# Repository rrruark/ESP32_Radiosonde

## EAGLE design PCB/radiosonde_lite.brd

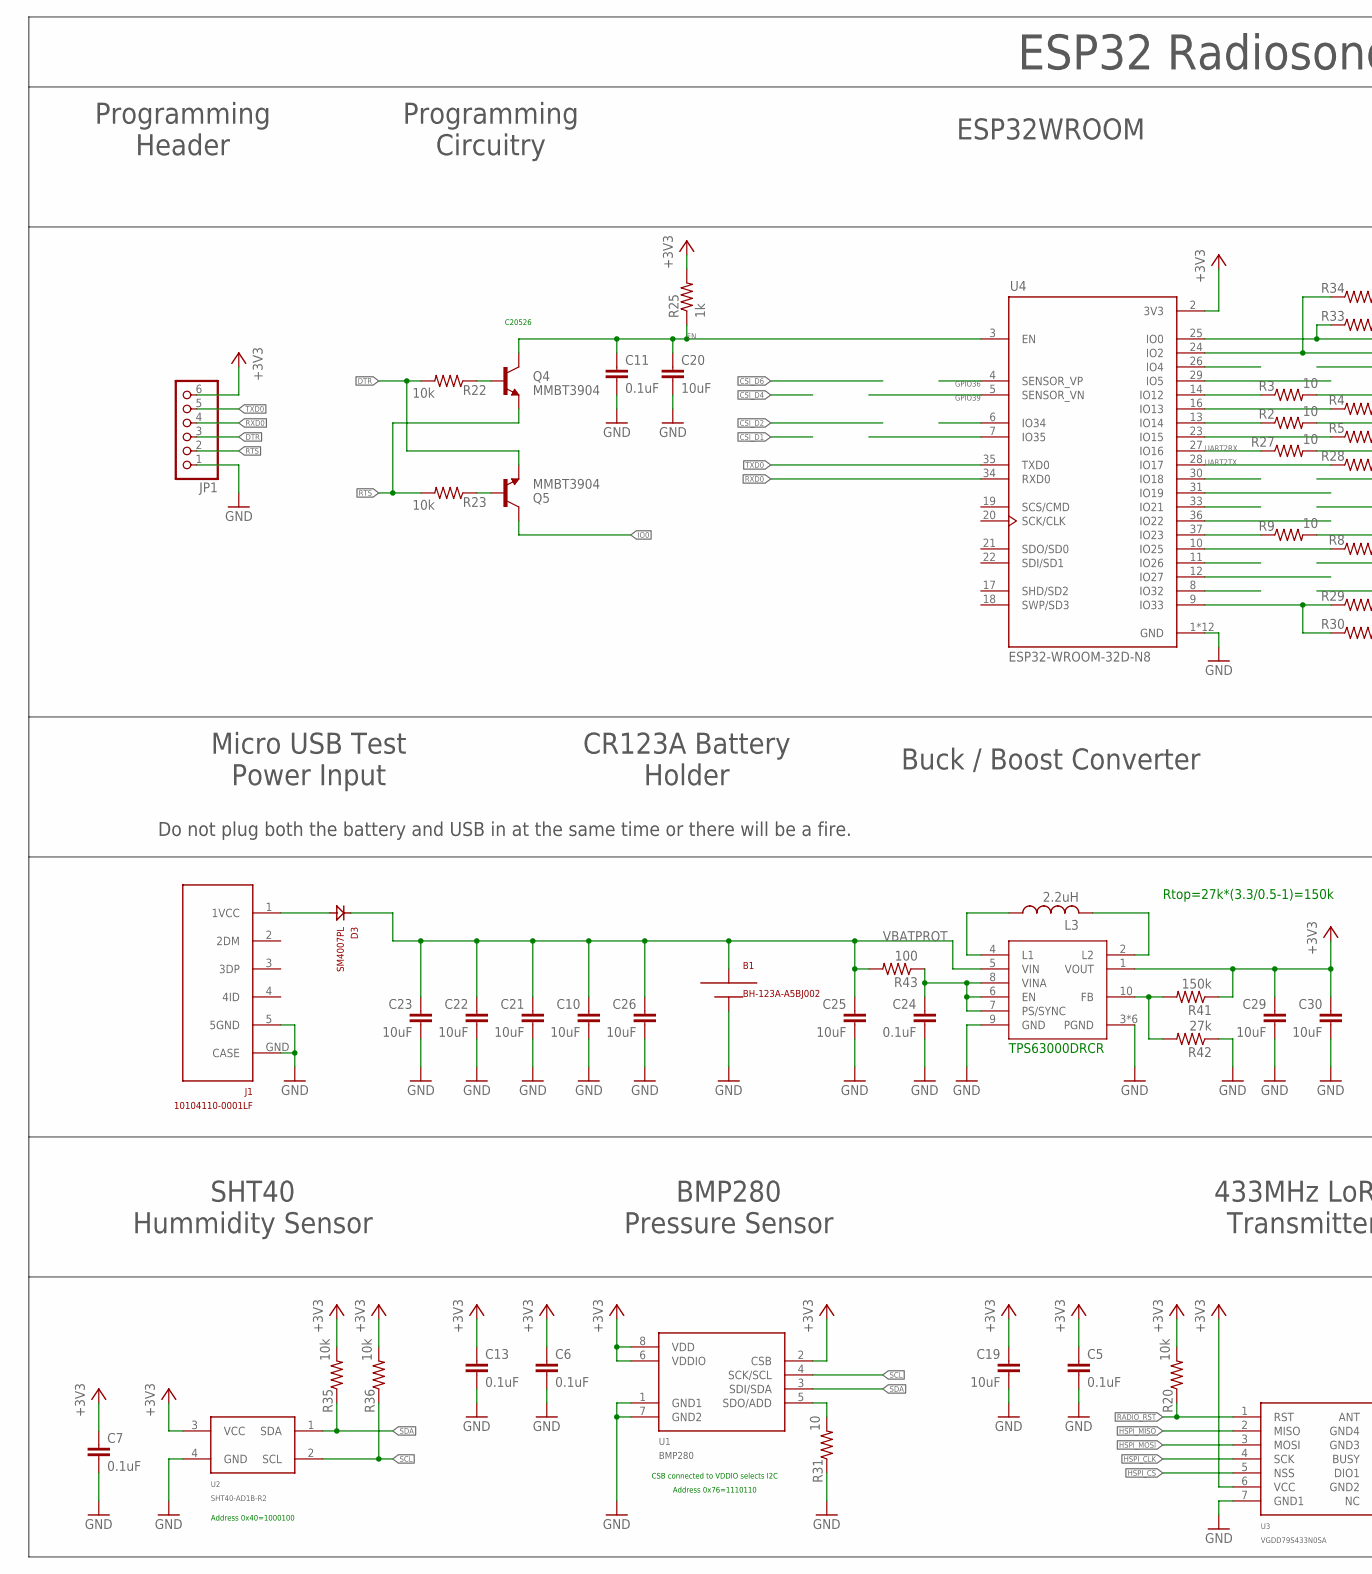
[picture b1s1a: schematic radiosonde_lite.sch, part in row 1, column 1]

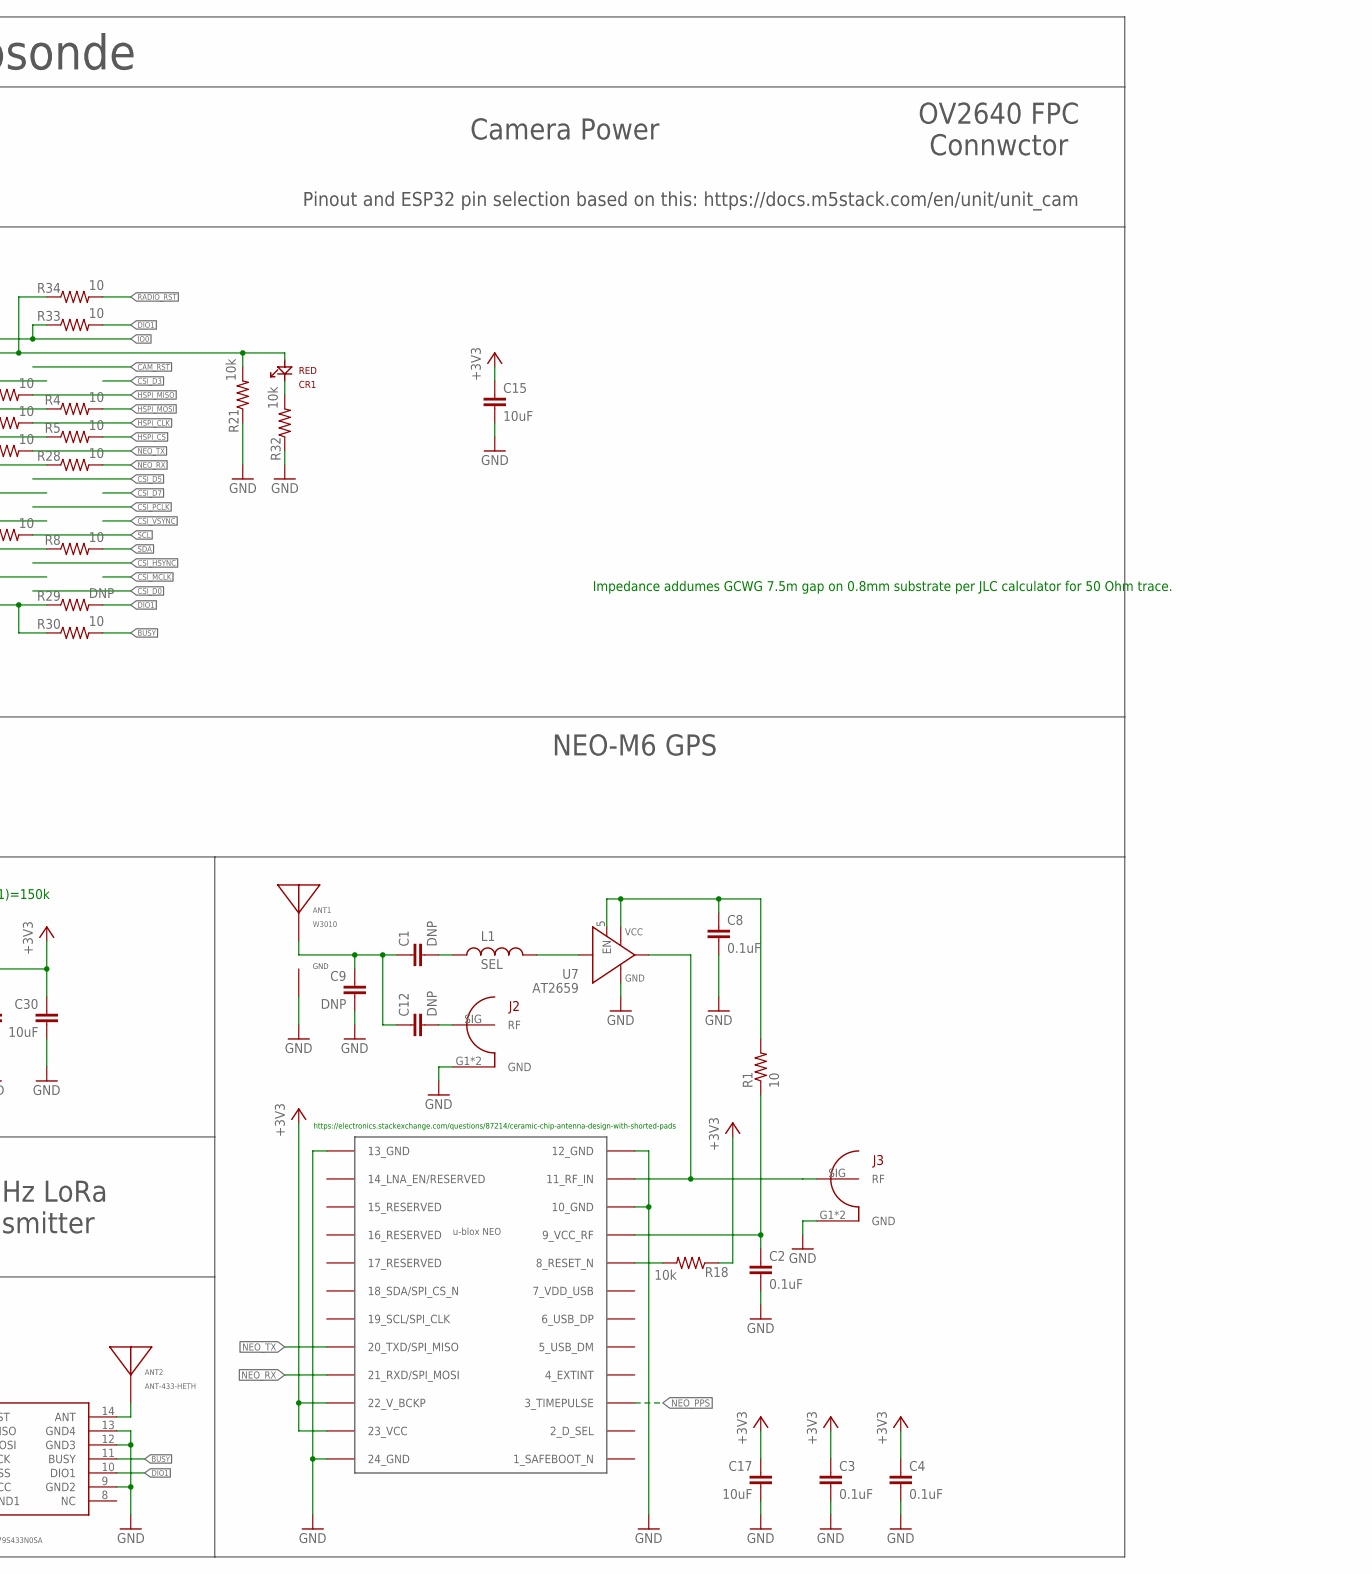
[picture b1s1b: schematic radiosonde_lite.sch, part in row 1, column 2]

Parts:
ANT1: W3010
ANT2: ANT-433-HETH
B1: BH-123A-A5BJ002
C1, C9, C12: DNP; 0402_INDUCTOR
C2, C3, C4, C5, C6, C7, C8, C11, C13: 0.1uF; 0402_INDUCTOR
C10, C15, C17, C19, C20, C21, C22, C23, C25, C26, C29, C30: 10uF; 0603
C24: 0.1uF; 0603
CR1: RED; 0603_DIODE
D3: SM4007PL; SOD123(AK)
IC1: NEO-M8
J1: 10104110-0001LF; MICRO_USB
J2, J3: CONUFL001-SMD; U.FL
JP1: PINHD-1X6; 1X06
L1: SEL; 0402_INDUCTOR
L3: 2.2uH; CY43
Q4, Q5: MMBT3904; SOT23-3_CENTERED
R1, R2, R3, R4, R5, R8, R9, R27, R28, R30, R31, R33, R34: 10; R0402
R18, R20, R21, R22, R23, R32, R35, R36: 10k; R0402
R25: 1k; 0603
R29: DNP; R0402
R41: 150k; 0603
R42: 27k; 0603
R43: 100; 0603
U1: BMP280; BME280
U2: SHT40-AD1B-R2; SHT40
U3: VGDD79S433N0SA
U4: ESP32-WROOM-32D-N8; MODULE_ESP32-WROOM-32D
U6: TPS63000DRCR; S-PVSON-N10
U7: AT2659; 6DFN-1X1.6

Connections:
+3V3: C3.P$1 (1), C4.P$1 (1), C5.P$1 (1), C6.P$1 (1), C7.P$1 (1), C13.P$1 (1), C15.1, C17.1, C19.1, C29.1, C30.1, IC1.22 (22_V_BCKP), IC1.23 (23_VCC), JP1.6, R18.1, R20.2, R25.2, R35.2, R36.2, R41.1, U1.2 (CSB), U1.6 (VDDIO), U1.8 (VDD), U2.3 (VCC), U3.6 (VCC), U4.2 (3V3), U6.1 (VOUT)
BUSY: R30.2, U3.11 (BUSY)
DIO1: R29.2, R33.2, U3.10 (DIO1)
DTR: JP1.3, Q5.2 (E), R22.2
EN: C11.P$1 (1), C20.1, Q4.3 (C), R25.1, U4.3 (EN)
GND: ANT1.P$1 (GND), ANT1.P$3 (GND), B1.N (-), C2.P$2 (2), C3.P$2 (2), C4.P$2 (2), C5.P$2 (2), C6.P$2 (2), C7.P$2 (2), C8.P$2 (2), C9.P$2 (2), C10.2, C11.P$2 (2), C13.P$2 (2), C15.2, C17.2, C19.2, C20.2, C21.2, C22.2, C23.2, C24.2, C25.2, C26.2, C29.2, C30.2, IC1.10 (10_GND), IC1.12 (12_GND), IC1.13 (13_GND), IC1.24 (24_GND), J1.5 (5GND), J1.GND (CASE), J2.G1 (GND), J2.G2 (GND), J3.G1 (GND), J3.G2 (GND), JP1.1, R21.1, R31.1, R32.1, R42.1, U1.1 (GND1), U1.7 (GND2), U2.4 (GND), U3.7 (GND1), U3.9 (GND2), U3.12 (GND3), U3.13 (GND4), U4.1 (GND), U4.15 (GND), U4.38 (GND), U4.39_1 (GND), U4.39_2 (GND), U4.39_3 (GND), U4.39_4 (GND), U4.39_5 (GND), U4.39_6 (GND), U4.39_7 (GND), U4.39_8 (GND), U4.39_9 (GND), U6.3 (PGND), U6.9 (GND), U6.PG (PGND), U6.PG1 (PGND), U6.PG2 (PGND), U6.PG3 (PGND), U6.PG4 (PGND), U7.1 (GND), U7.2 (GND)
GPIO36: U4.4 (SENSOR_VP)
GPIO39: U4.5 (SENSOR_VN)
GPS_VCC_RF: C8.P$1 (1), R1.2, U7.4 (VS), U7.5 (EN)
HSPI_CLK: R2.2, U3.4 (SCK)
HSPI_CS: R5.2, U3.5 (NSS)
HSPI_MISO: R3.2, U3.2 (MISO)
HSPI_MOSI: R4.2, U3.3 (MOSI)
IO0: Q5.3 (C), R33.1, U4.25 (IO0)
unnamed: R3.1, U4.14 (IO12)
unnamed: IC1.8 (8_RESET_N), R18.2
unnamed: C1.P$2 (2), L1.P$1
unnamed: R29.1, R30.1, U4.9 (IO33)
unnamed: L1.P$2, U7.3 (RF_IN)
unnamed: R4.1, U4.16 (IO13)
unnamed: R31.2, U1.5 (SDO/ADD)
unnamed: ANT2.IN1, ANT2.IN2, U3.14 (ANT)
unnamed: R5.1, U4.23 (IO15)
unnamed: ANT1.P$2 (ANT), C1.P$1 (1), C9.P$1 (1), C12.P$1 (1)
unnamed: CR1.K, R32.2
unnamed: R9.1, U4.37 (IO23)
unnamed: R8.1, U4.10 (IO25)
unnamed: Q4.1 (B), R22.1
unnamed: D3.A, J1.1 (1VCC)
unnamed: C2.P$1 (1), IC1.9 (9_VCC_RF), R1.1
unnamed: Q5.1 (B), R23.1
unnamed: CR1.A, R21.2, R34.1, U4.24 (IO2)
unnamed: R2.1, U4.13 (IO14)
unnamed: C12.P$2 (2), J2.SIG (RF)
unnamed: IC1.11 (11_RF_IN), J3.SIG (RF), U7.6 (RF_OUT)
unnamed: L3.P$1 (1), U6.4 (L1)
unnamed: L3.P$2 (2), U6.2 (L2)
unnamed: R41.2, R42.2, U6.10 (FB)
unnamed: C24.1, R43.1, U6.6 (EN), U6.7 (PS/SYNC), U6.8 (VINA)
NEO_PPS: IC1.3 (3_TIMEPULSE)
NEO_RX: IC1.21 (21_RXD/SPI_MOSI), R28.2
NEO_TX: IC1.20 (20_TXD/SPI_MISO), R27.2
RADIO_RST: R20.1, R34.2, U3.1 (RST)
RTS: JP1.2, Q4.2 (E), R23.2
RXD0: JP1.4, U4.34 (RXD0)
SCL: R9.2, R36.1, U1.4 (SCK/SCL), U2.2 (SCL)
SDA: R8.2, R35.1, U1.3 (SDI/SDA), U2.1 (SDA)
TXD0: JP1.5, U4.35 (TXD0)
UART2RX: R27.1, U4.27 (IO16)
UART2TX: R28.1, U4.28 (IO17)
VBATPROT: B1.P (+), C10.1, C21.1, C22.1, C23.1, C25.1, C26.1, D3.K, R43.2, U6.5 (VIN)

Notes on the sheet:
TPS63000DRCR
Rtop=27k*(3.3/0.5-1)=150k
https://electronics.stackexchange.com/questions/87214/ceramic-chip-antenna-design-with-shorted-pads
CSB connected to VDDIO selects I2C
Address 0x76=1110110
Address 0x40=1000100
ESP32 Radiosonde
Programming Header
Programming Circuitry
ESP32WROOM
Camera Power
OV2640 FPC Connwctor
Buck / Boost Converter
NEO-M6 GPS
433MHz LoRa Transmitter
BMP280 Pressure Sensor
SHT40 Hummidity Sensor
CR123A Battery Holder
Micro USB Test Power Input
Do not plug both the battery and USB in at the same time or there will be a fire.
Pinout and ESP32 pin selection based on this: https://docs.m5stack.com/en/unit/unit_cam
C20526
Impedance addumes GCWG 7.5m gap on 0.8mm substrate per JLC calculator for 50 Ohm trace.

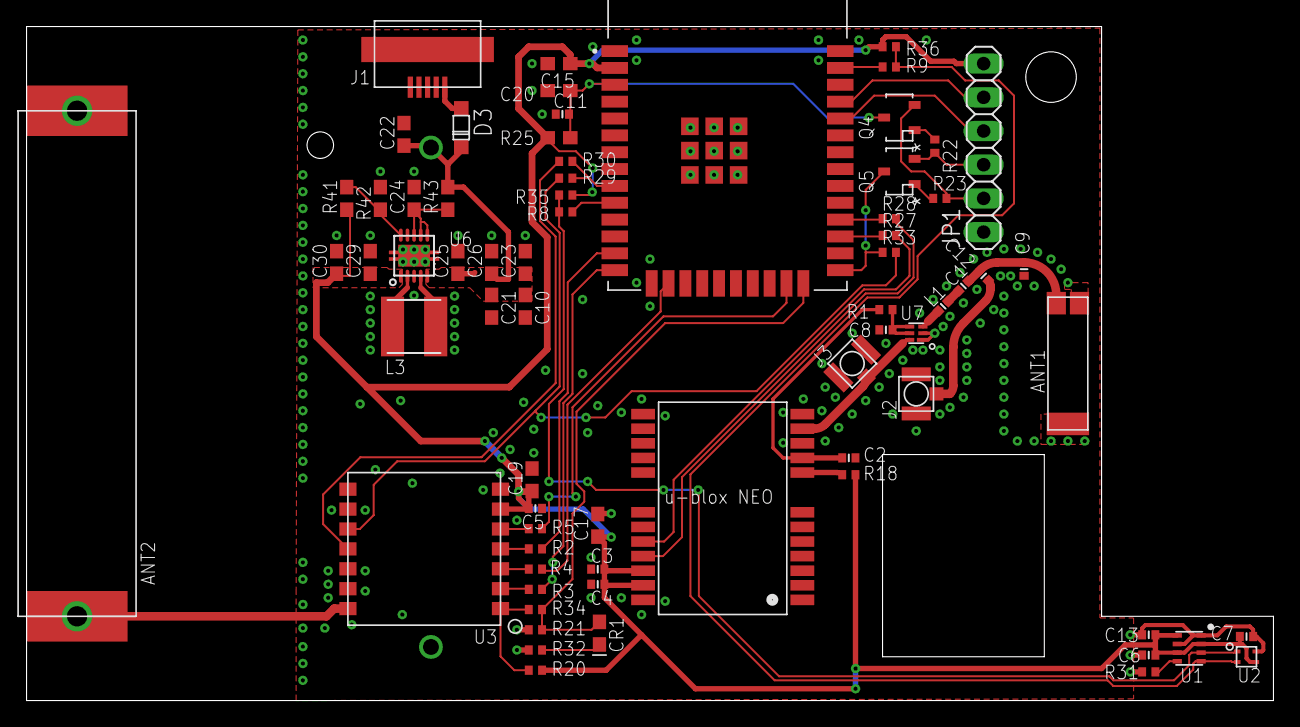
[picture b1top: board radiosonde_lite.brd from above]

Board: 2 copper layers, 94.0 x 50.8 mm, 71 parts (1 on the bottom side), 48 nets.

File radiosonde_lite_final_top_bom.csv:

Comment,Designator,Footprint,LCSC Part #
0.1uF,C2 C3 C4 C5 C6 C7 C11 C13 C14 C16,0402_INDUCTOR,
0.1uF,C24,0603,
1k,R8 R17,R0402,
2.2uH,L3,CY43,
6.8nH,L1,0402_INDUCTOR,
10,R1 R2 R3 R4 R5 R9 R10 R11 R12 R13 R15 R16 R27 R28 R31,R0402,
10k,R6 R7 R14 R18 R20 R21 R32 R35 R36,R0402,
10uF,C10 C15 C17 C19 C20 C21 C22 C23 C25 C26 C29 C30,0603,
22nF,C8,0402_INDUCTOR,
27k,R42,0603,
100,R43,0603,
150k,R41,0603,
220pF,C1,0402_INDUCTOR,
10104110-0001LF,J1,MICRO_USB,
ANT-433-HETH,ANT2,ANT-433-HETH,
ANT-916-HETH,ANT3,ANT-916-HETH,
AT2659,U7,6DFN-1X1.6,
BMP280,U1,BME280,
CONUFL001-SMD,J2 J3,U.FL,
DNP,C9 C12,0402_INDUCTOR,
ESP32-WROOM-32D-N8,U4,MODULE_ESP32-WROOM-32D,
NEO-M8,IC1,NEO-M8,
RED,CR1 CR2 CR3 CR4,0603_DIODE,
SHT40-AD1B-R2,U2,SHT40,
SM4007PL,D3,SOD123(AK),
TPS63000DRCR,U6,S-PVSON-N10,
VGDD79S433N0SA,U3,VGDD79S433N0SA,
W3010,ANT1,W3010,

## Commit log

2024-05-19 Initial Commit
    Ready for schematic review
2024-11-14 adding arduino code
2024-11-17 updating pdf
2024-12-13 Added Arduino sketches
2025-01-13 Removing WiFi
2025-01-17 Added mac serial number
2025-01-25 time
